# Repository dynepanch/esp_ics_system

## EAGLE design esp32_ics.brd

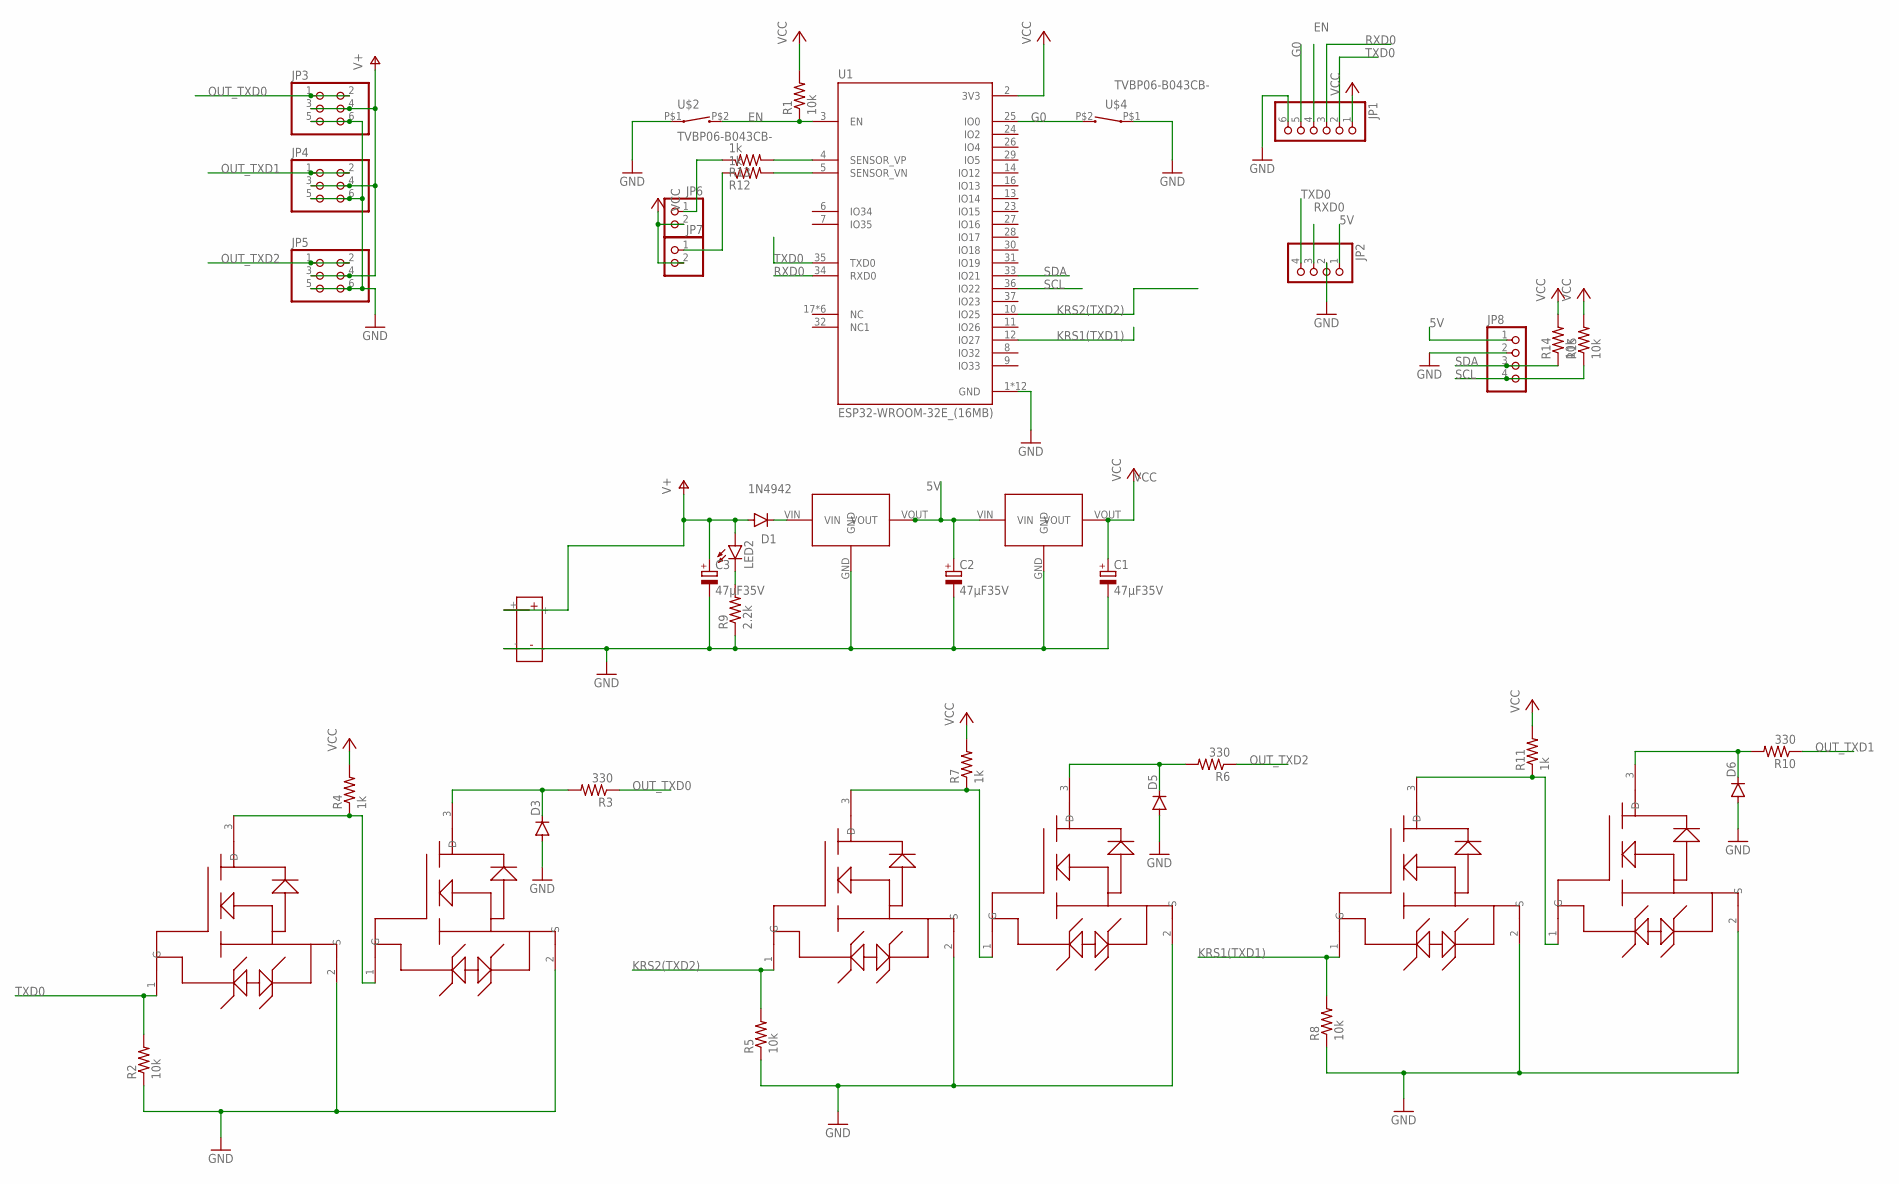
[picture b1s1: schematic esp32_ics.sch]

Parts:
C1, C2, C3: 47μF35V; E2-4
D1: 1N4942; DO41-10
D3, D5, D6: DIODE-SOD323-R; SOD323-R
JP1: PINHD-1X6; 1X06
JP2, JP8: PINHD-1X4; 1X04
JP3, JP4, JP5: PINHD-2X3/90; 2X03/90
JP6, JP7: PINHD-1X2; 1X02
LED2: LEDCHIP-LED0603; CHIP-LED0603
R1, R2, R5, R8, R14, R15: 10k; R0603
R3, R6, R10: 330; R0603
R4, R7, R11, R12, R13: 1k; R0603
R9: 2.2k; R0603
U1: ESP32-WROOM-32E_(16MB); XCVR_ESP32-WROOM-32E_(16MB)
U$1: BATT
U$2, U$4: TVBP06-B043CB-
U$5, U$6, U$7, U$8, U$9, U$10: BSS138; SOT23
ＮＪＭ２８４５ＤＬ１: 3.3v; TIP_3TANSI
ＮＪＭ７８０５ＳＤＬ１: 5v; TIP_3TANSI

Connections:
5V: C2.+, JP2.1, JP8.1, ＮＪＭ２８４５ＤＬ１.VIN, ＮＪＭ７８０５ＳＤＬ１.VOUT
EN: JP1.4, R1.1, U1.3 (EN), U$2.P$2 (2)
G0: JP1.5, U1.25 (IO0), U$4.P$2 (2)
GND: C1.-, C2.-, C3.-, D3.A, D5.A, D6.A, JP1.6, JP2.2, JP3.5, JP3.6, JP4.5, JP4.6, JP5.5, JP5.6, JP8.2, R2.1, R5.1, R8.1, R9.1, U1.1 (GND), U1.15 (GND), U1.38 (GND), U1.39_1 (GND), U1.39_2 (GND), U1.39_3 (GND), U1.39_4 (GND), U1.39_5 (GND), U1.39_6 (GND), U1.39_7 (GND), U1.39_8 (GND), U1.39_9 (GND), U$1.-, U$2.P$1 (1), U$4.P$1 (1), U$5.2 (S), U$6.2 (S), U$7.2 (S), U$8.2 (S), U$9.2 (S), U$10.2 (S), ＮＪＭ２８４５ＤＬ１.GND, ＮＪＭ７８０５ＳＤＬ１.GND
KRS1(TXD1): R8.2, U1.12 (IO27), U$9.1 (G)
KRS2(TXD2): R5.2, U1.10 (IO25), U$5.1 (G)
unnamed: R13.2, U1.4 (SENSOR_VP)
unnamed: R12.2, U1.5 (SENSOR_VN)
unnamed: LED2.C, R9.2
unnamed: R4.1, U$7.3 (D), U$8.1 (G)
unnamed: JP6.1, R13.1
unnamed: R7.1, U$5.3 (D), U$6.1 (G)
unnamed: JP7.1, R12.1
unnamed: R11.1, U$9.3 (D), U$10.1 (G)
unnamed: D1.C, ＮＪＭ７８０５ＳＤＬ１.VIN
OUT_TXD0: JP3.1, JP3.2, R3.1
OUT_TXD1: JP4.1, JP4.2, R10.1
OUT_TXD2: JP5.1, JP5.2, R6.1
RXD0: JP1.3, JP2.3, U1.34 (RXD0)
SCL: JP8.4, R15.1, U1.36 (IO22)
SDA: JP8.3, R14.1, U1.33 (IO21)
TXD0: JP1.2, JP2.4, R2.2, U1.35 (TXD0), U$7.1 (G)
TXD1: D3.C, R3.2, U$8.3 (D)
TXD2: D5.C, R6.2, U$6.3 (D)
TXD3: D6.C, R10.2, U$10.3 (D)
V+: C3.+, D1.A, JP3.3, JP3.4, JP4.3, JP4.4, JP5.3, JP5.4, LED2.A, U$1.+
VCC: C1.+, JP1.1, JP6.2, JP7.2, R1.2, R4.2, R7.2, R11.2, R14.2, R15.2, U1.2 (3V3), ＮＪＭ２８４５ＤＬ１.VOUT

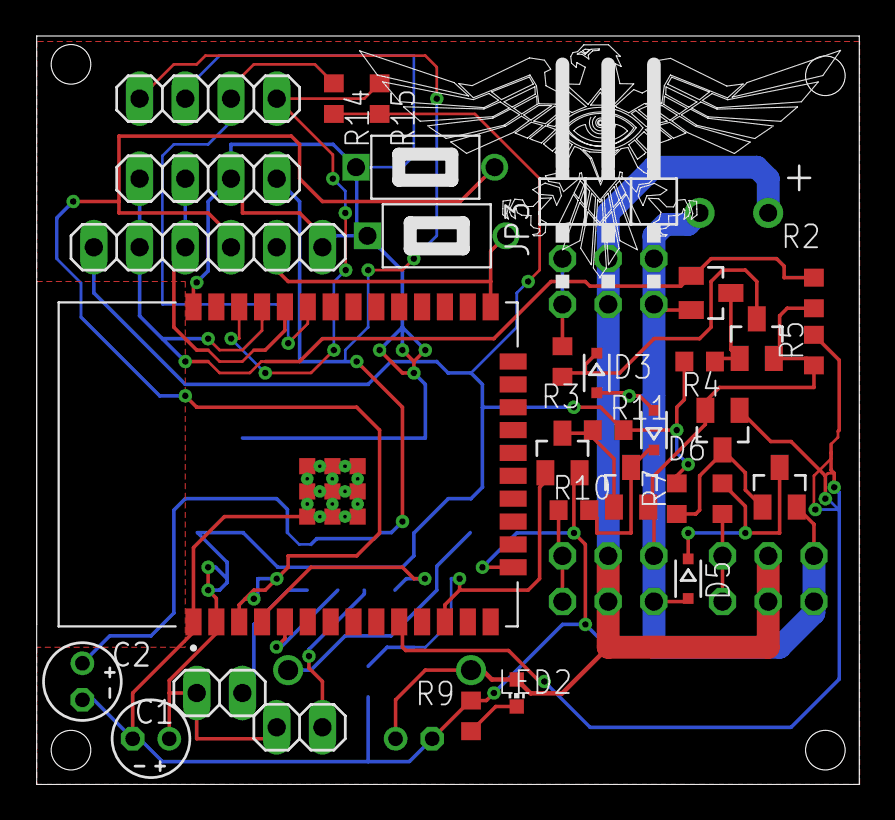
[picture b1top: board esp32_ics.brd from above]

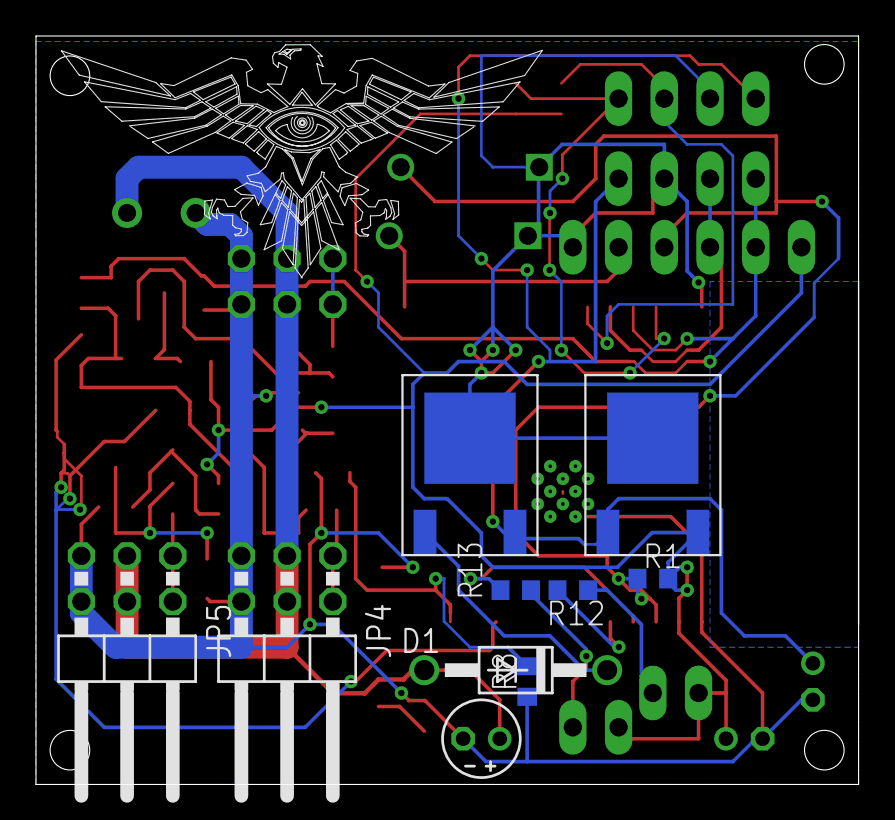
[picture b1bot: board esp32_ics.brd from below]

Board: 2 copper layers, 45.7 x 41.5 mm, 45 parts (11 on the bottom side), 27 nets.

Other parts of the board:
U$14, U$15: SHOKER
